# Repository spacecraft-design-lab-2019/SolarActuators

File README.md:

# SolarActuators
Team 3 Repository

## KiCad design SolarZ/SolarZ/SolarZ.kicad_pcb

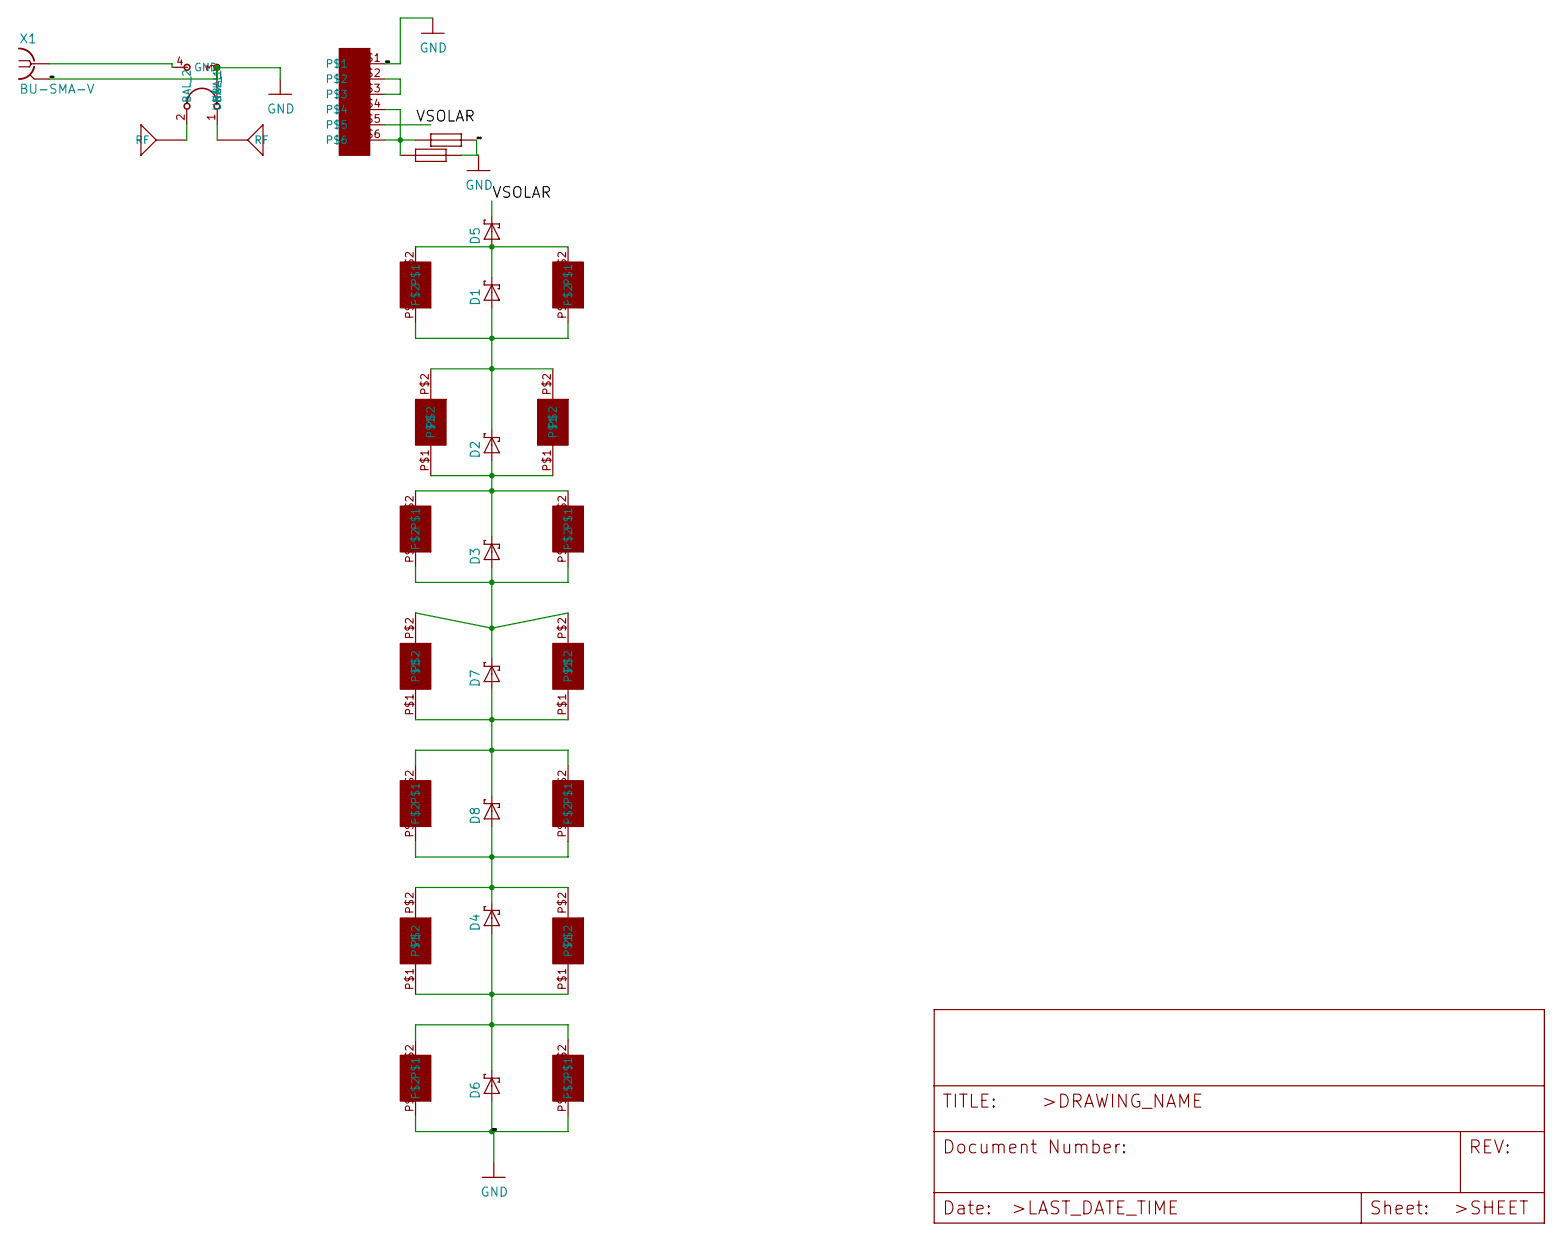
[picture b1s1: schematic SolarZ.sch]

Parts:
D1, D2, D3, D4, D5, D6, D7, D8: SB_DIODE
F1, F2: BURN_TERM; BURN_WIRE
U$1: BALUN
U$2, U$3: ANTENNA; TAPE
U$4: M20-8760342
UNK1, UNK6, UNK7, UNK10, UNK11, UNK13: KXOB22-04X3F
UNK2, UNK3, UNK4, UNK5, UNK8, UNK9, UNK12, UNK14: SLMD121H04L
X1: BU-SMA-V

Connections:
/VSOLAR: D5.NEG, U$4.P$5
GND: D6.POS, F1.2, F1.20 (2), F1.200 (2), F2.2, F2.20 (2), F2.200 (2), U$1.3 (UNBAL), U$4.P$1, UNK8.P$1, UNK9.P$1, X1.2, X1.3 (2), X1.4 (2), X1.5 (2)
unnamed: D1.NEG, D5.POS, UNK2.P$2, UNK3.P$2
unnamed: D1.POS, D2.NEG, UNK1.P$2, UNK2.P$1, UNK3.P$1, UNK13.P$2
unnamed: D2.POS, D3.NEG, UNK1.P$1, UNK4.P$2, UNK5.P$2, UNK13.P$1
unnamed: D3.POS, D7.NEG, UNK4.P$1, UNK5.P$1, UNK10.P$2, UNK11.P$2
unnamed: D4.NEG, D8.POS, UNK6.P$2, UNK7.P$2, UNK12.P$1, UNK14.P$1
unnamed: D4.POS, D6.NEG, UNK6.P$1, UNK7.P$1, UNK8.P$2, UNK9.P$2
unnamed: D7.POS, D8.NEG, UNK10.P$1, UNK11.P$1, UNK12.P$2, UNK14.P$2
unnamed: F1.1, F1.10 (1), F1.100 (1), F2.1, F2.10 (1), F2.100 (1), U$4.P$4, U$4.P$6
unnamed: U$1.1 (BAL_1), U$2.RF, U$2.RF_2
unnamed: U$1.2 (BAL_2), U$3.RF, U$3.RF_2
unnamed: U$4.P$2, U$4.P$3

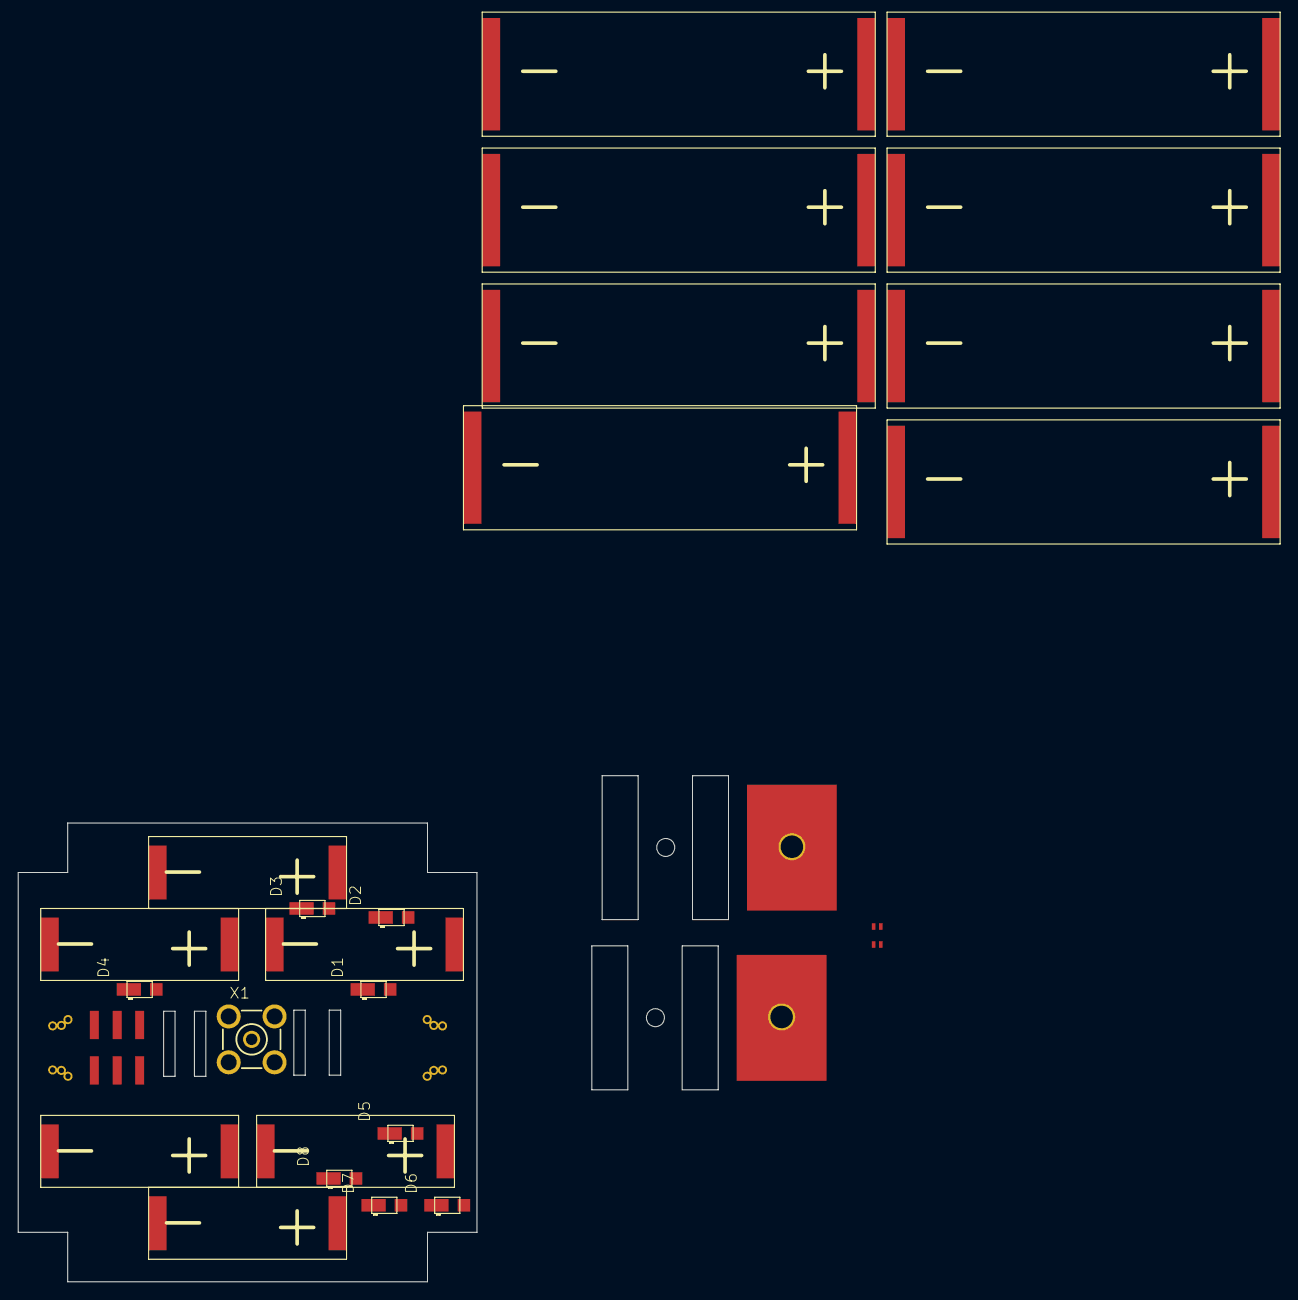
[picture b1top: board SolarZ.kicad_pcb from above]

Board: 4 copper layers, 29 parts (0 on the bottom side), 13 nets.

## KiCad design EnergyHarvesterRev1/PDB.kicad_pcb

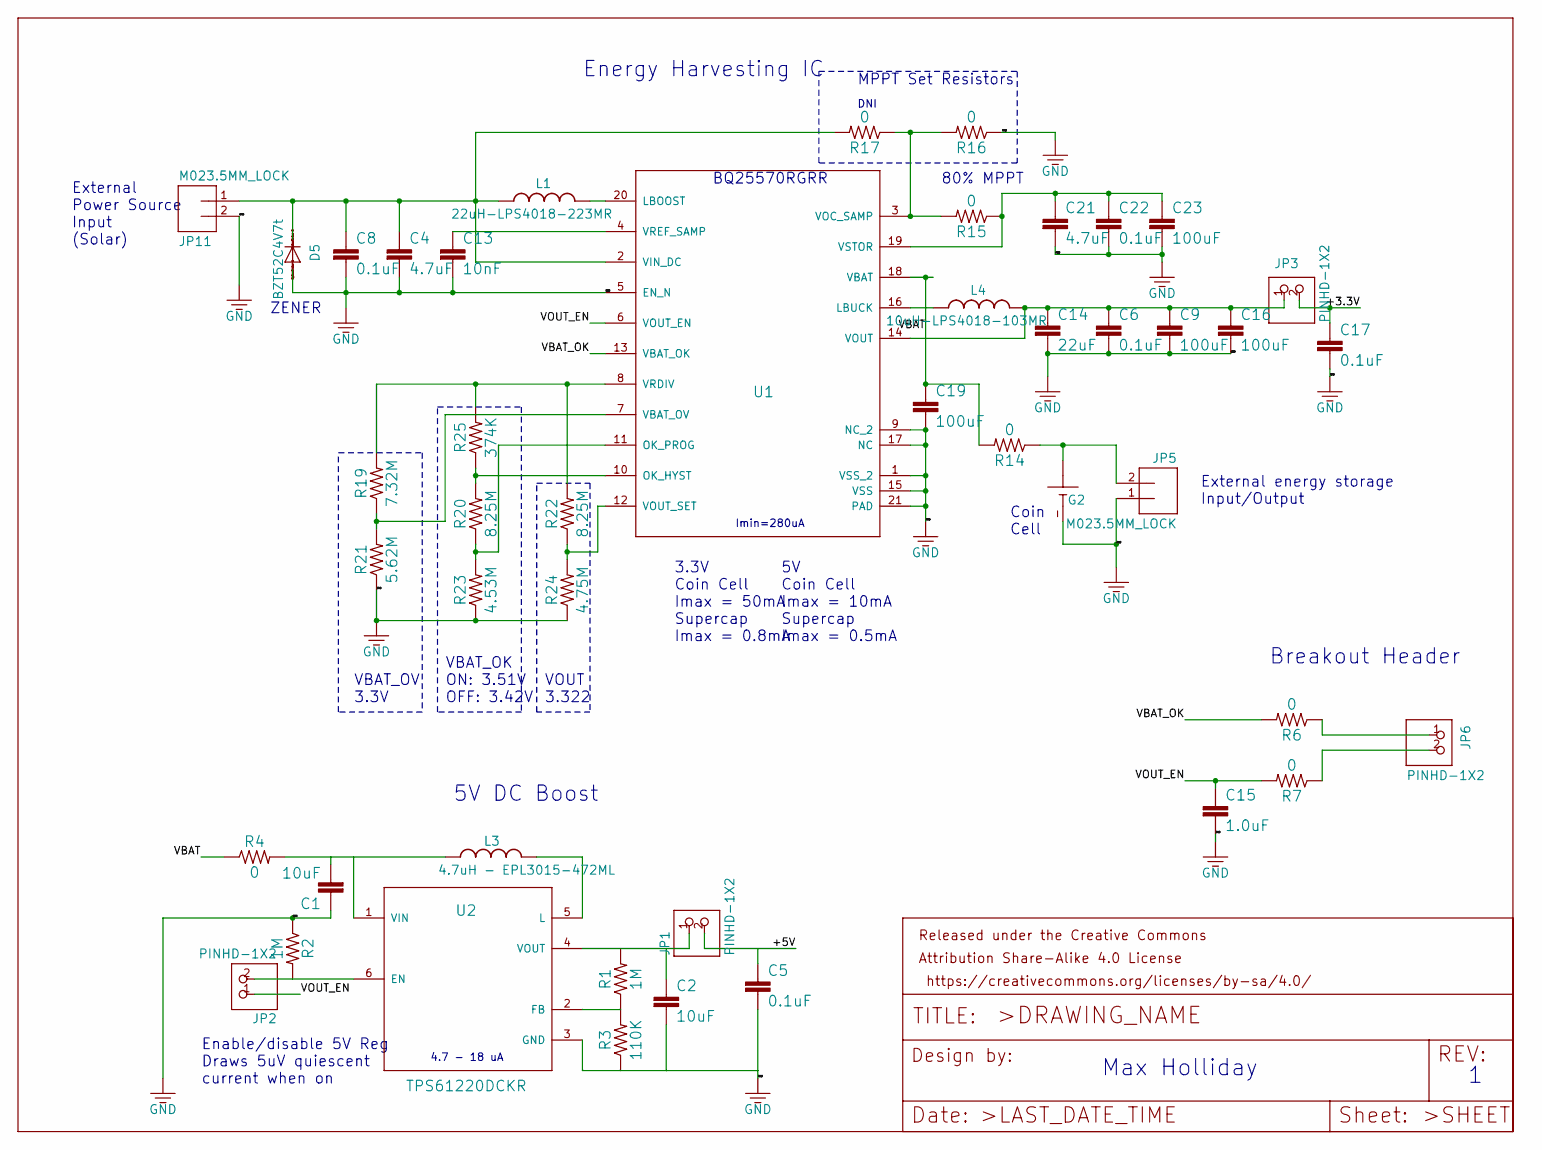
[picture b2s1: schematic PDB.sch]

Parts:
C1, C2: 10uF; 0603
C4, C21: 4.7uF; 0603
C5, C6, C8, C17, C22: 0.1uF; 0603
C9, C16, C19, C23: 100uF; 0603
C13: 10nF; 0603
C14: 22uF; 0805
C15: 1.0uF; 0603
D5: BZT52C4V7t; SOD523
FRAME1: FRAME-LETTERNO_PACKAGE; DUMMY
G2: 10MM_SM_COIN_CELL_CLIP
JP1, JP2, JP3, JP6: PINHD-1X2; 1X02
JP5, JP11: M023.5MM_LOCK; SCREWTERMINAL-3.5MM-2_LOCK
L1: 22uH-LPS4018-223MR; LPS4018
L3: 4.7uH - EPL3015-472ML; DFE322512C
L4: 10uH-LPS4018-103MR; LPS4018
R1, R2: 1M; 0603
R3: 110K; 0603
R4, R6, R7, R14, R15, R16, R17: 0; 0603
R19: 7.32M; 0603
R20, R22: 8.25M; 0603
R21: 5.62M; 0603
R23: 4.53M; 0603
R24: 4.75M; 0603
R25: 374K; 0603
U1: Value; RGR0020A
U2: TPS61220DCKR; DCK0006A

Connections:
3.3V: C1.1, C2.2, C4.2, C5.2, C6.2, C8.2, C9.2, C13.2, C14.2, C15.2, C16.2, C17.2, C19.2, C21.2, C22.2, C23.2, D5.A, G2.-, JP5.1, JP11.2, R2.1, R3.1, R16.1, R21.1, R23.1, R24.1, U1.1 (VSS_2), U1.5 (EN_N), U1.9 (NC_2), U1.15 (VSS), U1.17 (NC), U1.21 (PAD), U2.3 (GND)
/+3.3V: C17.1, JP3.2
/+5V: C5.1, JP1.2
/VBAT: C19.1, R4.1, R14.2, U1.18 (VBAT)
/VBAT_OK: R6.2, U1.13 (VBAT_OK)
/VOUT_EN: C15.1, JP2.1, R7.2, U1.6 (VOUT_EN)
unnamed: C1.2, L3.P$1 (1), R4.2, U2.1 (VIN)
unnamed: C2.1, JP1.1, R1.2, U2.4 (VOUT)
unnamed: C4.1, C8.1, D5.C, JP11.1, L1.1, R17.2, U1.2 (VIN_DC)
unnamed: C13.1, U1.4 (VREF_SAMP)
unnamed: C6.1, C9.1, C14.1, C16.1, JP3.1, L4.2, U1.14 (VOUT)
unnamed: C21.1, C22.1, C23.1, R15.1, U1.19 (VSTOR)
unnamed: G2.+@1 (+), G2.+@2 (+), JP5.2, R14.1
unnamed: JP2.2, R2.2, U2.6 (EN)
unnamed: JP6.1, R6.1
unnamed: JP6.2, R7.1
unnamed: L1.2, U1.20 (LBOOST)
unnamed: L3.P$2 (2), U2.5 (L)
unnamed: L4.1, U1.16 (LBUCK)
unnamed: R1.1, R3.2, U2.2 (FB)
unnamed: R15.2, R16.2, R17.1, U1.3 (VOC_SAMP)
unnamed: R19.1, R21.2, U1.7 (VBAT_OV)
unnamed: R19.2, R22.2, R25.2, U1.8 (VRDIV)
unnamed: R20.1, R23.2, U1.11 (OK_PROG)
unnamed: R20.2, R25.1, U1.10 (OK_HYST)
unnamed: R22.1, R24.2, U1.12 (VOUT_SET)

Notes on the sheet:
DNI
ZENER
VOUT 3.322
80% MPPT
VBAT_OK ON: 3.51V OFF: 3.42V
VBAT_OV 3.3V
Enable/disable 5V Reg Draws 5uV quiescent current when on
3.3V Coin Cell Imax = 50mA Supercap Imax = 0.8mA
5V Coin Cell Imax = 10mA Supercap Imax = 0.5mA
4.7 - 18 uA
Imin=280uA
Coin Cell
External Power Source Input (Solar)
MPPT Set Resistors
External energy storage Input/Output
BQ25570RGRR
Max Holliday
5V DC Boost
Energy Harvesting IC
Breakout Header

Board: 2 copper layers, 47 parts (0 on the bottom side), 26 nets, no tracks yet.

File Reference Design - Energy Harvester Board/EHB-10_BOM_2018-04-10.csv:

Part,Value,Device,Package,Description,ALTERNATEPARTNUMBER,APPLICATION_BUILDNUMBER,COMPTYPE,DESIGNER,MANUFACTURER,MOUNTTYPE,PACKAGEREFERENCE,PARTNUMBER,PIN_COUNT,PROD_ID,REFDES,ROHS,TYPE,VALUE,VERSION
C1,10uF,10UF-0603-6.3V-20%,603,10.0µF ceramic capacitors,,,,,,,,,,CAP-11015,,,,10uF,
C2,10uF,10UF-0603-6.3V-20%,603,10.0µF ceramic capacitors,,,,,,,,,,CAP-11015,,,,10uF,
C4,4.7uF,4.7UF0603,603,4.7µF ceramic capacitors,,,,,,,,,,CAP-08280,,,,4.7uF,
C5,0.1uF,0.1UF-0603-25V-(+80/-20%),603,0.1µF ceramic capacitors,,,,,,,,,,CAP-00810,,,,0.1uF,
C6,0.1uF,0.1UF-0603-25V-(+80/-20%),603,0.1µF ceramic capacitors,,,,,,,,,,CAP-00810,,,,0.1uF,
C8,0.1uF,0.1UF-0603-25V-(+80/-20%),603,0.1µF ceramic capacitors,,,,,,,,,,CAP-00810,,,,0.1uF,
C9,100uF,0.1UF-0603-25V-(+80/-20%),603,0.1µF ceramic capacitors,,,,,,,,,,CAP-00810,,,,0.1uF,
C13,10nF,10NF-0603-50V-10%,603,0.01uF/10nF/10,,,,,,,,,,,,,,,
C14,22uF,22UF-0805-6.3V-20%,805,22µF ceramic capacitors,,,,,,,,,,CAP-08402,,,,22uF,
C15,1.0uF,1.0UF-0603-16V-10%,603,1µF ceramic capacitors,,,,,,,,,,CAP-00868,,,,1.0uF,
C16,100uF,0.1UF-0603-25V-(+80/-20%),603,0.1µF ceramic capacitors,,,,,,,,,,CAP-00810,,,,0.1uF,
C17,0.1uF,0.1UF-0603-25V-(+80/-20%),603,0.1µF ceramic capacitors,,,,,,,,,,CAP-00810,,,,0.1uF,
C19,100uF,0.1UF-0603-25V-(+80/-20%),603,0.1µF ceramic capacitors,,,,,,,,,,CAP-00810,,,,0.1uF,
C21,4.7uF,4.7UF0603,603,4.7µF ceramic capacitors,,,,,,,,,,CAP-08280,,,,4.7uF,
C22,0.1uF,0.1UF-0603-25V-(+80/-20%),603,0.1µF ceramic capacitors,,,,,,,,,,CAP-00810,,,,0.1uF,
C23,100uF,0.1UF-0603-25V-(+80/-20%),603,0.1µF ceramic capacitors,,,,,,,,,,CAP-00810,,,,0.1uF,
D5,BZT52C4V7t,DIODE-SOD523,SOD523,DIODE,,,,,,,,,,,,,,,
FRAME1,FRAME-LETTERNO_PACKAGE,FRAME-LETTERNO_PACKAGE,DUMMY,Schematic Frame - Letter,,,,Nobody,,,,,,,,,,,v01
G2,10MM_SM_COIN_CELL_CLIP,10MM_SM_COIN_CELL_CLIP,10MM_SM_COIN_CELL_CLIP,Battery cell clip for CR927,,,,,,,,,,,,,,,
JP1,,PINHD-1X2,1X02,PIN HEADER,,,,,,,,,,,,,,,
JP2,,PINHD-1X2,1X02,PIN HEADER,,,,,,,,,,,,,,,
JP3,,PINHD-1X2,1X02,PIN HEADER,,,,,,,,,,,,,,,
JP5,M023.5MM_LOCK,M023.5MM_LOCK,SCREWTERMINAL-3.5MM-2_LOCK,"Standard 2-pin 0.1 header. Use with""",,,,,,,,,,CONN-08399,,,,,
JP6,,PINHD-1X2,1X02,PIN HEADER,,,,,,,,,,,,,,,
JP11,M023.5MM_LOCK,M023.5MM_LOCK,SCREWTERMINAL-3.5MM-2_LOCK,"Standard 2-pin 0.1 header. Use with""",,,,,,,,,,CONN-08399,,,,,
L1,22uH-LPS4018-223MR,COILCRAFT-LPS4018,LPS4018,Coilcraft,,,,,,,,,,,,,,,
L3,4.7uH - EPL3015-472ML,INDUCTORDFE322512C,DFE322512C,A very specific inductor,,,,,,,,,,,,,,,
L4,10uH-LPS4018-103MR,COILCRAFT-LPS4018,LPS4018,Coilcraft,,,,,,,,,,,,,,,
R1,1M,1MOHM-0603-1/4W-5%,603,1MO resistor,,,,,,,,,,RES-07868,,,,1M,
R2,1M,1MOHM-0603-1/4W-5%,603,1MO resistor,,,,,,,,,,RES-07868,,,,1M,
R3,110K,100KOHM-0603-1/10W-1%,603,100kO resistor,,,,,,,,,,RES-07828,,,,100k,
R4,0,0OHM-0603-1/10W-5%,603,0O resistor,,,,,,,,,,RES-08609,,,,0,
R6,0,0OHM-0603-1/10W-5%,603,0O resistor,,,,,,,,,,RES-08609,,,,0,
R7,0,0OHM-0603-1/10W-5%,603,0O resistor,,,,,,,,,,RES-08609,,,,0,
R14,0,0OHM-0603-1/10W-5%,603,0O resistor,,,,,,,,,,RES-08609,,,,0,
R15,0,0OHM-0603-1/10W-5%,603,0O resistor,,,,,,,,,,RES-08609,,,,0,
R16,0,0OHM-0603-1/10W-5%,603,0O resistor,,,,,,,,,,RES-08609,,,,0,
R17,0,0OHM-0603-1/10W-5%,603,0O resistor,,,,,,,,,,RES-08609,,,,0,
R19,7.32M,1MOHM-0603-1/4W-5%,603,1MO resistor,,,,,,,,,,RES-07868,,,,1M,
R20,8.25M,1MOHM-0603-1/4W-5%,603,1MO resistor,,,,,,,,,,RES-07868,,,,1M,
R21,5.62M,1MOHM-0603-1/4W-5%,603,1MO resistor,,,,,,,,,,RES-07868,,,,1M,
R22,8.25M,1MOHM-0603-1/4W-5%,603,1MO resistor,,,,,,,,,,RES-07868,,,,1M,
R23,4.53M,1MOHM-0603-1/4W-5%,603,1MO resistor,,,,,,,,,,RES-07868,,,,1M,
R24,4.75M,1MOHM-0603-1/4W-5%,603,1MO resistor,,,,,,,,,,RES-07868,,,,1M,
R25,374K,1MOHM-0603-1/4W-5%,603,1MO resistor,,,,,,,,,,RES-07868,,,,1M,
U1,Value,BQ25570RGRR,RGR0020A,,BQ25570RGRT,*,IC,,Texas Instruments,SMT,RGR0020A,BQ25570RGRR,21,,RefDes,Y,TYPE,Value,
U2,TPS61220DCKR,TPS61220DCKR,DCK0006A,,,,IC,,Texas Instruments,SMT,DCK0006A,TPS61220DCK,6,,RefDes,Y,TYPE,Value,

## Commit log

2019-10-08 Create Charging circuit reference
2019-10-08 Added datasheet for charging IC
2019-10-09 Example solar cell & torquer designs from PandaSat
2019-10-10 Added power over orbit calculator
2019-10-11 adding bq25570 example design and datasheet
2019-10-13 Added magnetorquer references
2019-10-14 Added blank files for the new PCB layout
2019-10-14 Added components + lib to board!
2019-10-21 Set up directory for antenna/+Z board.
2019-10-21 Added sub-files, did early layout and cleanup.
2019-10-21 Preliminary layout, pending updates from AV about radio.
2019-10-24 add referece document for parallel operation.
2019-10-28 PCB test log file added
2019-10-30 Added energy circuit test notes
2019-10-31 Added updates power over orbit calculations
2019-11-12 Update test report for diode lamp_light
2019-11-12 Created main.py for burn wire testing
    Save this to a trinket M0 and play with the duty_cycle variable to find the optimal duty cycle for safe burning
2019-11-12 New testing report added
2019-12-09 Reference document for energy harvest board testing is added.
2019-12-09 Voltage plot is added.
2019-12-09 Add Vin < Vout(i.e., EXT BAT) testing voltage plot
2019-12-12 Detailed energy harvest board testing report
